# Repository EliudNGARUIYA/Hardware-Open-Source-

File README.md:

# Hardware-Open-Source-
Random hardware projects I'm working on like this one here on Home Automation...

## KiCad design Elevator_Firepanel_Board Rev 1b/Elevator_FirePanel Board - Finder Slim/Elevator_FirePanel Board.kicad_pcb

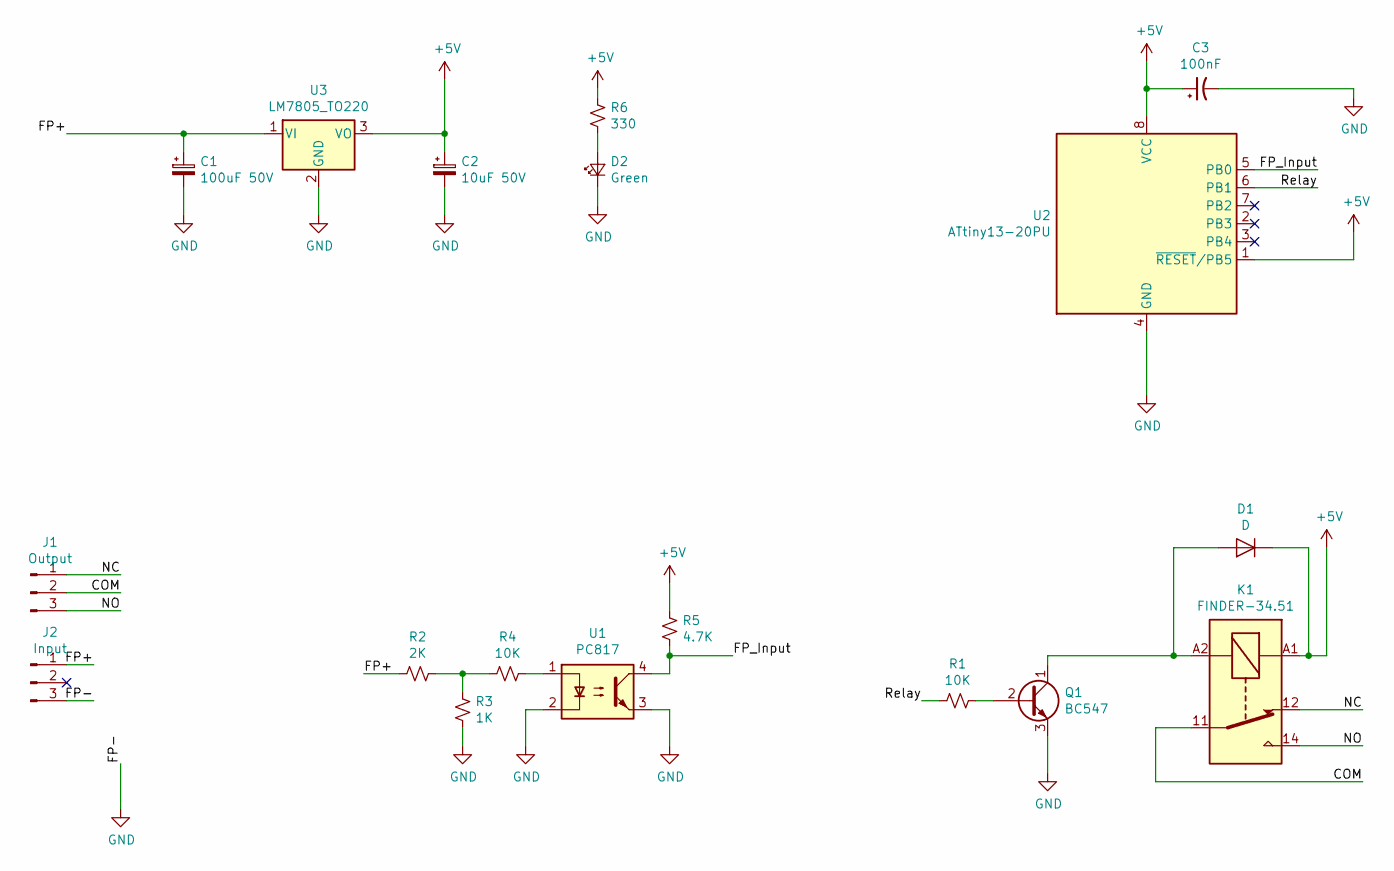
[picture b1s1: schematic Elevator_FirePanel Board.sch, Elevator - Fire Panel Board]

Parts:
C1: 100uF 50V; CP_Radial_D8.0mm_P2.50mm
C2: 10uF 50V; CP_Radial_D8.0mm_P2.50mm
C3: 100nF; CP_Radial_Tantal_D4.5mm_P2.50mm
D1: D; D_5W_P12.70mm_Horizontal
D2: Green; LED_D3.0mm
J1: Output; PhoenixContact_MSTBA_2,5_3-G_1x03_P5.00mm_Horizontal
J2: Input; Wago_734-133_1x03_P3.50mm_Vertical
K1: FINDER-34.51; Relay_SPDT_Finder_34.51_Vertical
Q1: BC547; TO-92_Inline
R1, R4: 10K; R_Axial_DIN0207_L6.3mm_D2.5mm_P10.16mm_Horizontal
R2: 2K; R_Axial_DIN0207_L6.3mm_D2.5mm_P10.16mm_Horizontal
R3: 1K; R_Axial_DIN0207_L6.3mm_D2.5mm_P10.16mm_Horizontal
R5: 4.7K; R_Axial_DIN0207_L6.3mm_D2.5mm_P10.16mm_Horizontal
R6: 330; R_Axial_DIN0207_L6.3mm_D2.5mm_P10.16mm_Horizontal
U1: PC817; DIP-4_W7.62mm
U2: ATtiny13-20PU; DIP-8_W7.62mm
U3: LM7805_TO220; TO-220-3_Vertical

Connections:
+5V: C2.1, C3.1, D1.1 (K), K1.A1, R5.2, R6.2, U2.1 (~RESET~/PB5), U2.8 (VCC), U3.3 (VO)
/COM: J1.2, K1.11
/FP+: C1.1, J2.1, R2.2, U3.1 (VI)
/FP_Input: R5.1, U1.4, U2.5 (PB0)
/NC: J1.1, K1.12
/NO: J1.3, K1.14
/Relay: R1.2, U2.6 (PB1)
GND: C1.2, C2.2, C3.2, D2.1 (K), J2.3, Q1.3 (E), R3.1, U1.2, U1.3, U2.4 (GND), U3.2 (GND)
unnamed: D1.2 (A), K1.A2, Q1.1 (C)
unnamed: D2.2 (A), R6.1
unnamed: Q1.2 (B), R1.1
unnamed: R2.1, R3.2, R4.2
unnamed: R4.1, U1.1

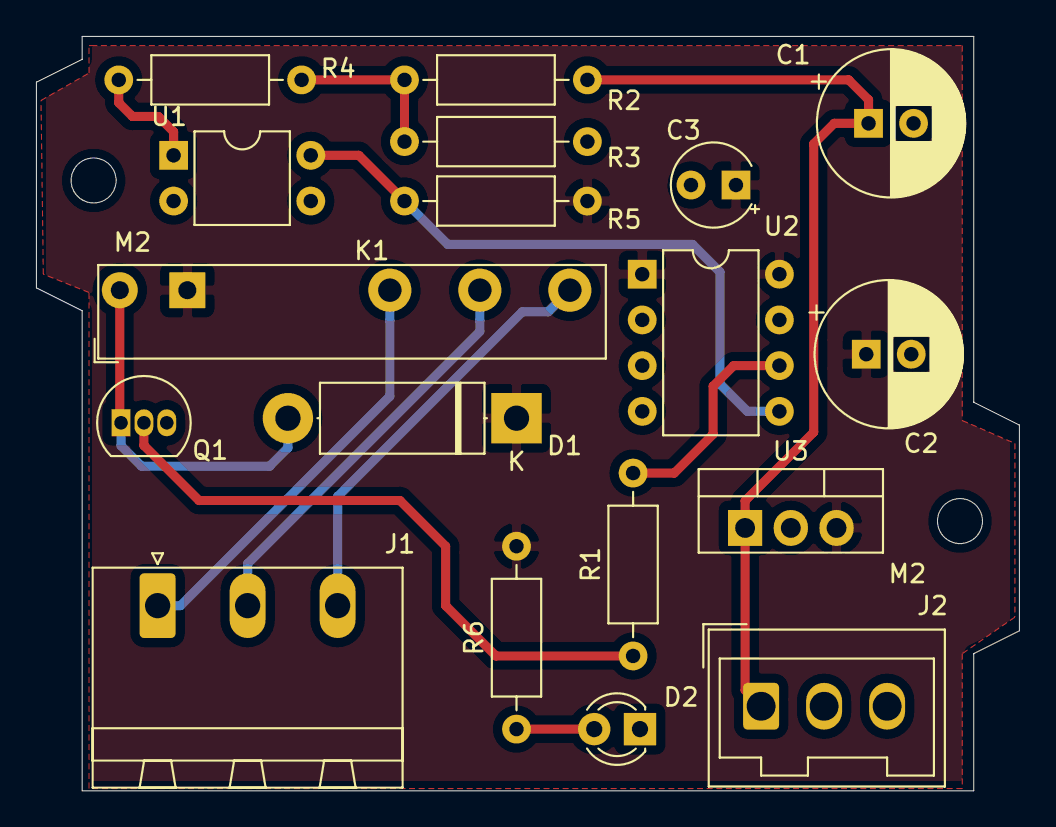
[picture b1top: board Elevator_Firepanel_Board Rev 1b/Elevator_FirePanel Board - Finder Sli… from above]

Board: 2 copper layers, 54.6 x 41.9 mm, 20 parts (0 on the bottom side), 13 nets.

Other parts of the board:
M2, M2#2: MountingHole_2.5mm

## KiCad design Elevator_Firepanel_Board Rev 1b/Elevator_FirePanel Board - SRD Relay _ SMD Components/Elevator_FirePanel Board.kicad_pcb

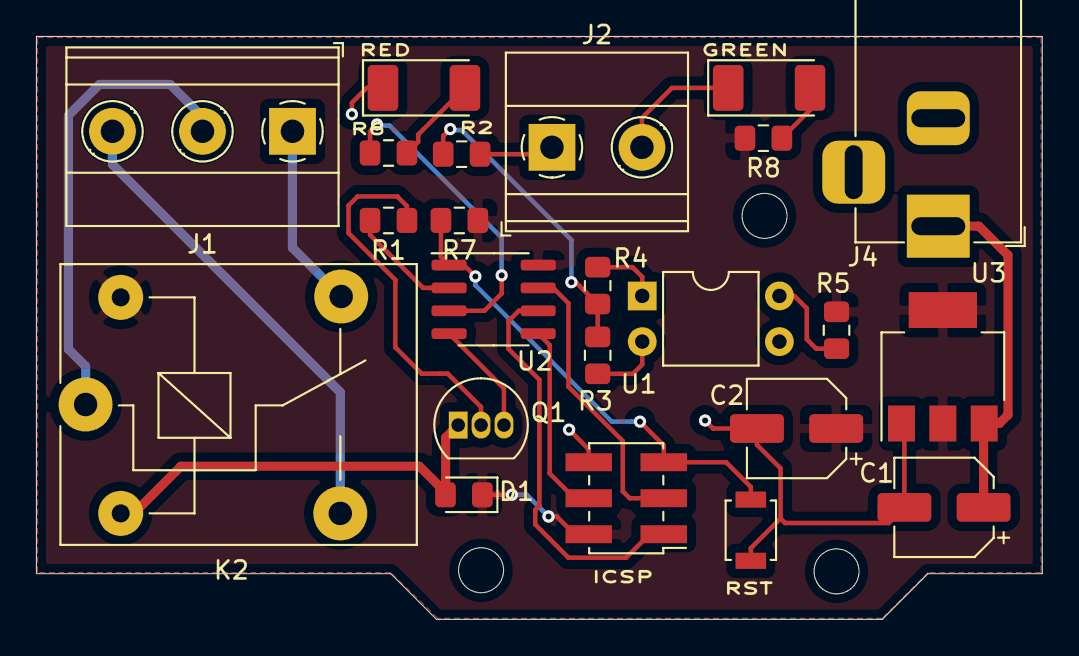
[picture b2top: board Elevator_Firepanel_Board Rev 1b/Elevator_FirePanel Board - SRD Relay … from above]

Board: 2 copper layers, 55.9 x 32.4 mm, 23 parts (0 on the bottom side), 20 nets.

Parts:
C1: 100uF 35V; CP_Elec_5x5.4
C2: 10uF 35V; CP_Elec_5x5.4
D1: D; D_0805_2012Metric_Pad1.15x1.40mm_HandSolder
GREEN: LED; LED_2010_5025Metric_Castellated
ICSP: ICSP; PinHeader_2x03_P2.00mm_Vertical_SMD
J1: Output; TerminalBlock_Phoenix_MKDS-1,5-3_1x03_P5.00mm_Horizontal
J2: Input; TerminalBlock_Phoenix_MKDS-1,5-2_1x02_P5.00mm_Horizontal
J4: DC_IN; BarrelJack_Horizontal
K2: SANYOU_SRD_Form_C; Relay_SPDT_SANYOU_SRD_Series_Form_C
Q1: BC547; TO-92_Inline
R1, R4, R7: 10K; R_0805_2012Metric_Pad1.15x1.40mm_HandSolder
R2: 2K; R_0805_2012Metric_Pad1.15x1.40mm_HandSolder
R3: 1K; R_0805_2012Metric_Pad1.15x1.40mm_HandSolder
R5: 4.7K; R_0805_2012Metric_Pad1.15x1.40mm_HandSolder
R6, R8: 330; R_0805_2012Metric_Pad1.15x1.40mm_HandSolder
RED: Green; LED_2010_5025Metric_Castellated
RST: SW_Push; SW_SPST_B3U-1000P
U1: PC817; DIP-4_W7.62mm
U2: ATtiny13-20SSU; SOIC-8_3.9x4.9mm_P1.27mm
U3: AMS1117-5.0; SOT-223-3_TabPin2

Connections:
+5V: C2.1, D1.1, ICSP.2, K2.5, R5.2, R7.1, R8.2, U2.8, U3.2
+12V: C1.1, J4.1, U3.3
/FP_Input: R5.1, U1.4
/Rela_y: R6.2, U2.3
/Relay: R1.2, U2.2
GND: C1.2, C2.2, GREEN.1, ICSP.6, J2.2, J4.2, Q1.3, R3.1, RED.1, RST.2, U1.2, U1.3, U2.4, U3.1
MISO: ICSP.1, U2.6
MOSI: ICSP.4, U2.5
unnamed: D1.2, K2.2, Q1.1
unnamed: R6.1, RED.2
unnamed: GREEN.2, R8.1
unnamed: J1.1, K2.4
unnamed: J1.2, K2.1
unnamed: J1.3, K2.3
unnamed: J2.1, R2.2
unnamed: Q1.2, R1.1
unnamed: R2.1, R3.2, R4.2
unnamed: R4.1, U1.1
PB2: ICSP.3, U2.7
Reset: ICSP.5, R7.2, RST.1, U2.1

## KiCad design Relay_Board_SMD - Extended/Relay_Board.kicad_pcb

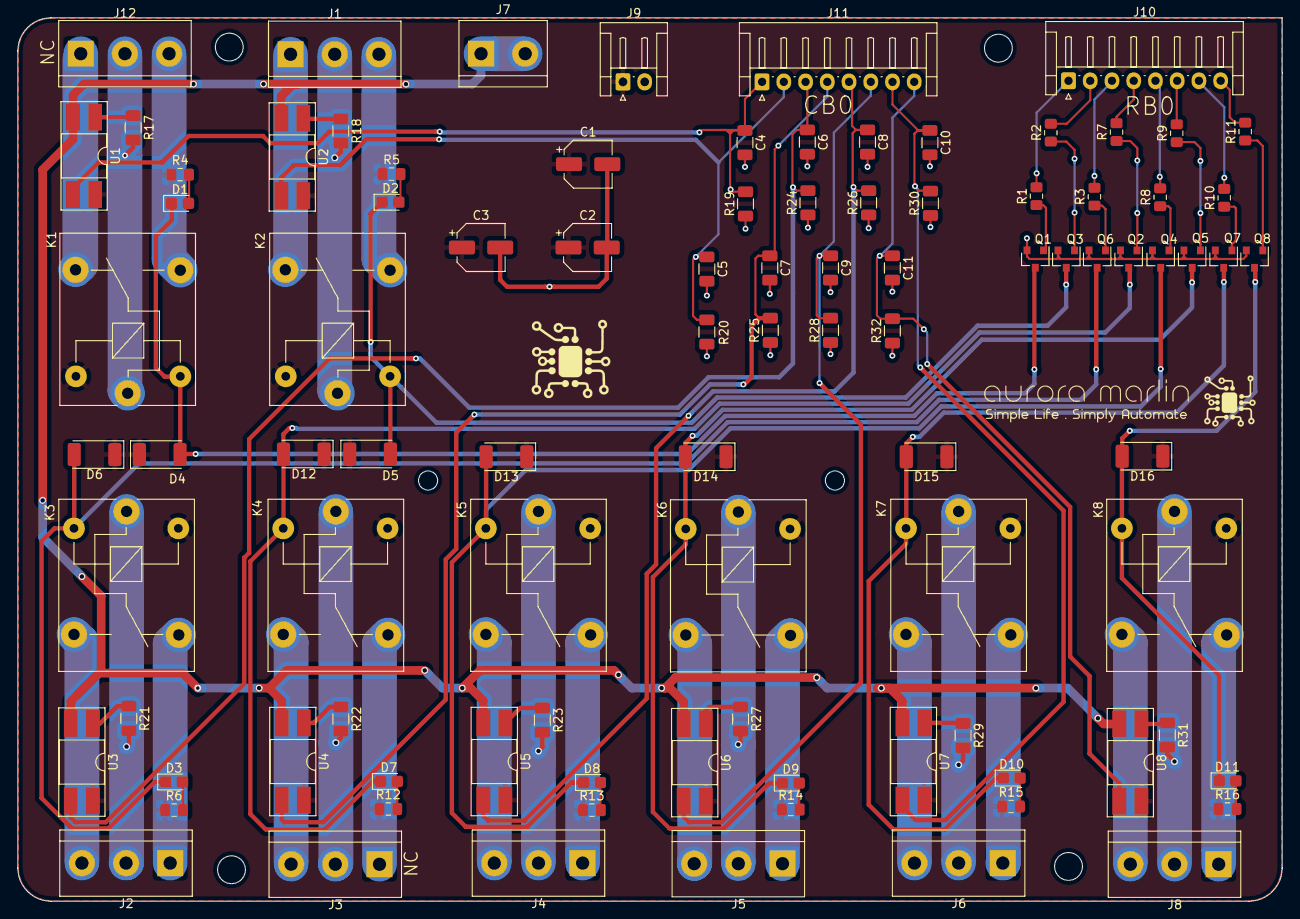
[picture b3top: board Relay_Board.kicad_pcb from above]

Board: 2 copper layers, 145.4 x 101.6 mm, 95 parts (0 on the bottom side), 75 nets.

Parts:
C1: 470uF 25V; CP_Elec_5x5.4
C2: 100uF 25V; CP_Elec_5x5.4
C3: 10uF 25v; CP_Elec_5x5.4
C4, C5, C6, C7, C8, C9, C10, C11: 10uF; C_1206_3216Metric
D1, D2, D3, D7, D8, D9, D10, D11: RED; LED_0805_2012Metric_Castellated
D4, D5, D6, D12, D13, D14, D15, D16: 1N4007; D_2010_5025Metric_Pad1.52x2.65mm_HandSolder
J1, J2, J3, J4, J5, J6, J8, J12: Relay OUT; TerminalBlock_bornier-3_P5.08mm
J7: AC_IN; TerminalBlock_bornier-2_P5.08mm
J9: 5VDC; JST_EH_S2B-EH_1x02_P2.50mm_Horizontal
J10: MCU; JST_EH_S8B-EH_1x08_P2.50mm_Horizontal
J11: OPTO; JST_EH_S8B-EH_1x08_P2.50mm_Horizontal
K1, K2, K3, K4, K5, K6, K7, K8: SANYOU_SRD_Form_C; Relay_SPDT_SANYOU_SRD_Series_Form_C
Q1, Q2, Q3, Q4, Q5, Q6, Q7, Q8: BC847; SOT-23
R1, R2, R3, R7, R8, R9, R10, R11: 10K; R_0805_2012Metric_Pad1.15x1.40mm_HandSolder
R4, R5, R6, R12, R13, R14, R15, R16: 330; R_0805_2012Metric_Pad1.15x1.40mm_HandSolder
R17, R18, R21, R22, R23, R27, R29, R31: 200K; R_1206_3216Metric
R19, R20, R24, R25, R26, R28, R30, R32: 100K; R_1206_3216Metric
U1, U2, U3, U4, U5, U6, U7, U8: EL814; DIP-4_W8.89mm_SMDSocket_LongPads

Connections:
240_N: J7.1, J7.2, U1.2, U2.2, U3.2, U4.2, U5.2, U6.2, U7.2, U8.2
+5V: C1.1, C2.1, C3.1, D4.1, D5.1, D6.1, D12.1, D13.1, D14.1, D15.1, D16.1, J9.1, K1.5, K2.5, K3.5, K4.5, K5.5, K6.5, K7.5, K8.5, R4.1, R5.1, R6.1, R12.1, R13.1, R14.1, R15.1, R16.1, U1.4, U2.4, U3.4, U4.4, U5.4, U6.4, U7.4, U8.4
/L1: J12.1, K1.4
/L2: J1.1, K2.4
/L3: J2.1, K3.4
/L4: J3.1, K4.4
/L5: J4.1, K5.4
/L6: J5.1, K6.4
/L7: J6.1, K7.4
/L8: J8.1, K8.4
/RR_1: J12.3, K1.3
/RR_2: J1.3, K2.3
/RR_3: J2.3, K3.3
/RR_4: J3.3, K4.3
/RR_5: J4.3, K5.3
/RR_6: J5.3, K6.3
/RR_7: J6.3, K7.3
/RR_8: J8.3, K8.3
/Relay_1: J10.1, R1.2
/Relay_2: J10.2, R2.2
/Relay_3: J10.3, R3.2
/Relay_4: J10.4, R7.2
/Relay_5: J10.5, R8.2
/Relay_6: J10.6, R9.2
/Relay_7: J10.7, R10.2
/Relay_8: J10.8, R11.2
COM1: J12.2, K1.1, R17.2
COM2: J1.2, K2.1, R18.2
COM3: J2.2, K3.1, R21.2
COM4: J3.2, K4.1, R22.2
COM5: J4.2, K5.1, R23.2
COM6: J5.2, K6.1, R27.2
COM7: J6.2, K7.1, R29.2
COM8: J8.2, K8.1, R31.2
GND: C1.2, C2.2, C3.2, C4.2, C5.2, C6.2, C7.2, C8.2, C9.2, C10.2, C11.2, J9.2, Q1.2, Q2.2, Q3.2, Q4.2, Q5.2, Q6.2, Q7.2, Q8.2, R19.1, R20.1, R24.1, R25.1, R26.1, R28.1, R30.1, R32.1
unnamed: D1.1, D4.2, K1.2, Q1.3
unnamed: D1.2, R4.2
unnamed: D2.1, D5.2, K2.2, Q3.3
unnamed: D2.2, R5.2
unnamed: D3.1, D6.2, K3.2, Q6.3
unnamed: D3.2, R6.2
unnamed: D7.2, R12.2
unnamed: D8.2, R13.2
unnamed: D9.2, R14.2
unnamed: D10.1, D15.2, K7.2, Q7.3
unnamed: D10.2, R15.2
unnamed: D11.1, D16.2, K8.2, Q8.3
unnamed: D11.2, R16.2
unnamed: D7.1, D12.2, K4.2, Q2.3
unnamed: D8.1, D13.2, K5.2, Q4.3
unnamed: D9.1, D14.2, K6.2, Q5.3
unnamed: Q1.1, R1.1
unnamed: Q2.1, R7.1
unnamed: Q3.1, R2.1
unnamed: Q4.1, R8.1
unnamed: Q5.1, R9.1
unnamed: Q6.1, R3.1
unnamed: Q7.1, R10.1
unnamed: Q8.1, R11.1
unnamed: R17.1, U1.1
unnamed: R18.1, U2.1
unnamed: R21.1, U3.1
unnamed: R22.1, U4.1
unnamed: R23.1, U5.1
unnamed: R27.1, U6.1
unnamed: R29.1, U7.1
unnamed: R31.1, U8.1
OUT1: C4.1, J11.1, R19.2, U1.3
OUT2: C5.1, J11.2, R20.2, U2.3
OUT3: C6.1, J11.3, R24.2, U3.3
OUT4: C7.1, J11.4, R25.2, U4.3
OUT5: C8.1, J11.5, R26.2, U5.3
OUT6: C9.1, J11.6, R28.2, U6.3
OUT7: C10.1, J11.7, R30.2, U7.3
OUT8: C11.1, J11.8, R32.2, U8.3

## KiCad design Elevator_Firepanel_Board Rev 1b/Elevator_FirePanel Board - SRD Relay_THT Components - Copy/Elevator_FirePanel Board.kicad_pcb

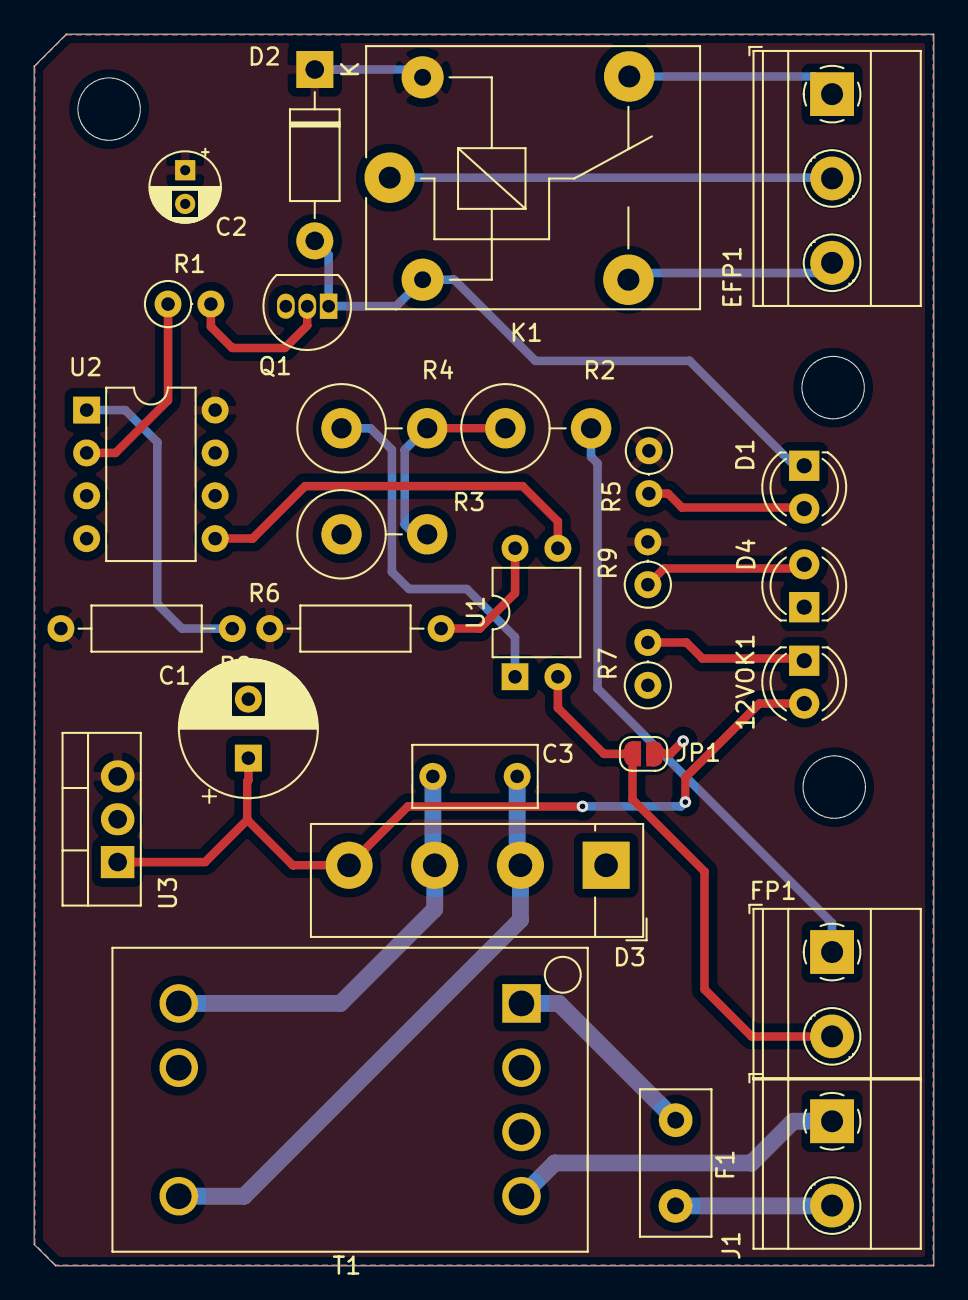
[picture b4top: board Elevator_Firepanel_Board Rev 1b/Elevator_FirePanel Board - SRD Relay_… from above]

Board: 2 copper layers, 53.3 x 73.0 mm, 28 parts (0 on the bottom side), 24 nets.

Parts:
12VOK1: Blue; LED_D4.0mm
C1: 100uF 35V; CP_Radial_D8.0mm_P3.50mm
C2: 10uF 35V; CP_Radial_D4.0mm_P2.00mm
C3: 1uF 400V; C_Rect_L7.2mm_W3.5mm_P5.00mm_FKS2_FKP2_MKS2_MKP2
D1: Red; LED_D4.0mm
D2: 1N4001; D_DO-41_SOD81_P10.16mm_Horizontal
D3: D_Bridge_-AA+; Diode_Bridge_Vishay_KBL
D4: Green; LED_D4.0mm
EFP1: Output; TerminalBlock_Phoenix_MKDS-1,5-3_1x03_P5.00mm_Horizontal
F1: 2A; Fuse_Littelfuse_395Series
FP1: Input; TerminalBlock_Phoenix_MKDS-1,5-2_1x02_P5.00mm_Horizontal
J1: AC_IN; TerminalBlock_Phoenix_MKDS-1,5-2_1x02_P5.00mm_Horizontal
JP1: GROUND; SolderJumper-2_P1.3mm_Open_RoundedPad1.0x1.5mm
K1: SANYOU_SRD_Form_C; Relay_SPDT_SANYOU_SRD_Series_Form_C
Q1: BC547; TO-92_Inline
R1: 10K; R_Axial_DIN0207_L6.3mm_D2.5mm_P2.54mm_Vertical
R2: 2K 1/2W; R_Axial_DIN0516_L15.5mm_D5.0mm_P5.08mm_Vertical
R3: 1K 1/2W; R_Axial_DIN0516_L15.5mm_D5.0mm_P5.08mm_Vertical
R4: 10K 1/2W; R_Axial_DIN0516_L15.5mm_D5.0mm_P5.08mm_Vertical
R5, R7, R9: 330; R_Axial_DIN0207_L6.3mm_D2.5mm_P2.54mm_Vertical
R6: 4.7K; R_Axial_DIN0207_L6.3mm_D2.5mm_P10.16mm_Horizontal
R8: 10K; R_Axial_DIN0207_L6.3mm_D2.5mm_P10.16mm_Horizontal
T1: Transformer_1P_1S_SO8; Transformer_Microphone_Lundahl_LL1587
U1: PC817; DIP-4_W7.62mm
U2: ATtiny13-20PU; DIP-8_W7.62mm
U3: LM7805_TO220; TO-220-3_Vertical

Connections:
+5V: C2.1, D2.1, K1.5, R5.1, R6.2, R8.1, R9.2, U2.8, U3.3
+12V: 12VOK1.2, C1.1, D3.4, U3.1
/ACL: F1.2, J1.2
/ACL_2: C3.1, D3.2, T1.8
/ACN: J1.1, T1.4
/ACN_2: C3.2, D3.3, T1.5
/Relay: R1.1, U2.2
GND: C1.2, C2.2, D3.1, D4.1, JP1.2, Q1.3, R3.1, R7.1, U2.4, U3.2
MOSI: U1.3, U2.5
unnamed: 12VOK1.1, R7.2
unnamed: D1.1, D2.2, K1.2, Q1.1
unnamed: D1.2, R5.2
unnamed: D4.2, R9.1
unnamed: EFP1.1, K1.4
unnamed: EFP1.2, K1.1
unnamed: EFP1.3, K1.3
unnamed: F1.1, T1.1
unnamed: FP1.1, R2.2
unnamed: FP1.2, JP1.1, U1.2
unnamed: Q1.2, R1.2
unnamed: R2.1, R3.2, R4.2
unnamed: R4.1, U1.1
unnamed: R6.1, U1.4
Reset: R8.2, U2.1

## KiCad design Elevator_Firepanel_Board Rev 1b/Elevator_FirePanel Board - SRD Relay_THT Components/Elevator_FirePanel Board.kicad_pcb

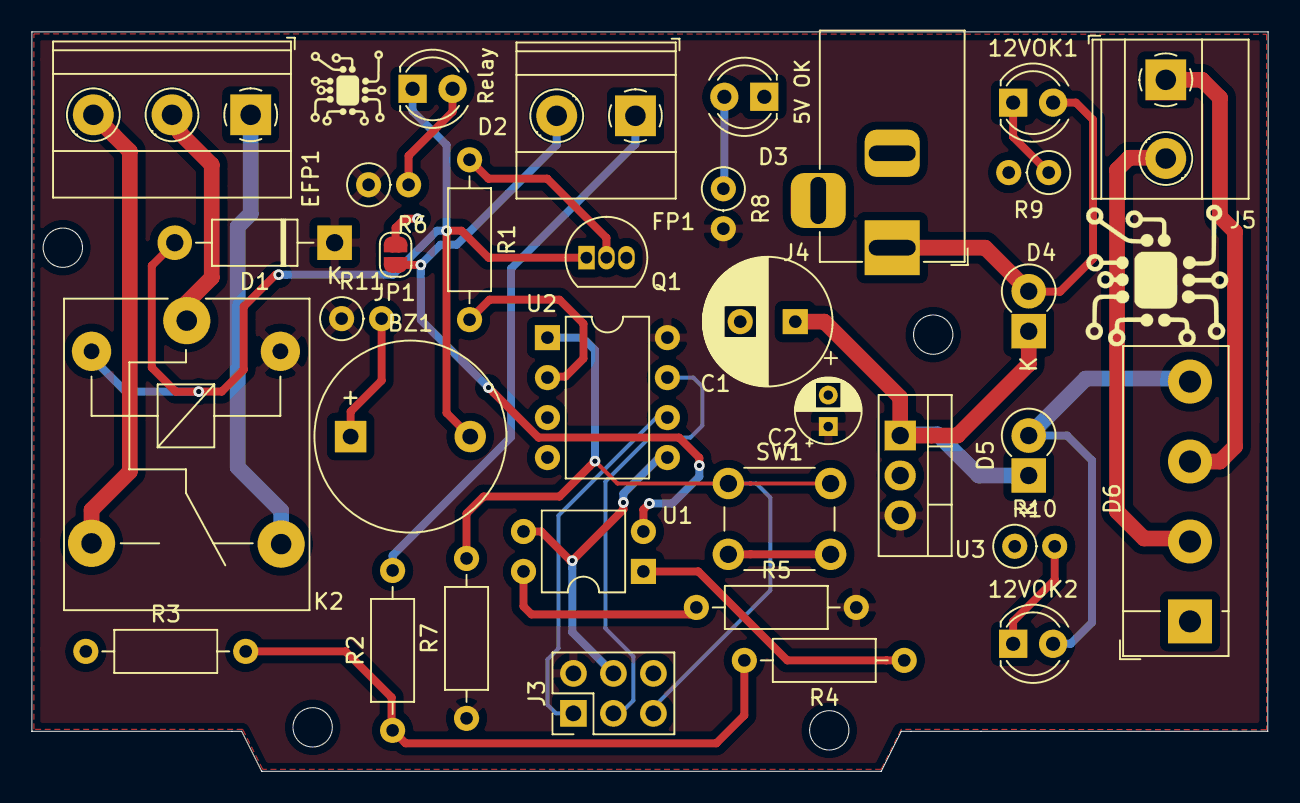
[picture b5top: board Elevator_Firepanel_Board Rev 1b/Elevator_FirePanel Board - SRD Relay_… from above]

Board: 2 copper layers, 78.6 x 47.0 mm, 34 parts (0 on the bottom side), 27 nets.

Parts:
12VOK1: Yellow; LED_D4.0mm
12VOK2: Blue; LED_D4.0mm
BZ1: Buzzer; Buzzer_12x9.5RM7.6
C1: 100uF 35V; CP_Radial_D8.0mm_P3.50mm
C2: 10uF 35V; CP_Radial_D4.0mm_P2.00mm
D1: 1N4001; D_DO-41_SOD81_P10.16mm_Horizontal
D2: Red; LED_D4.0mm
D3: Green; LED_D4.0mm
D4, D5: D; D_DO-41_SOD81_P2.54mm_Vertical_KathodeUp
D6: D_Bridge_-AA+; Diode_Bridge_Vishay_KBL
EFP1: Output; TerminalBlock_Phoenix_MKDS-1,5-3_1x03_P5.00mm_Horizontal
FP1: Input; TerminalBlock_Phoenix_MKDS-1,5-2_1x02_P5.00mm_Horizontal
J3: ICSP; PinHeader_2x03_P2.54mm_Vertical
J4: DC_IN; BarrelJack_Horizontal
J5: AC_IN; TerminalBlock_Phoenix_MKDS-1,5-2_1x02_P5.00mm_Horizontal
JP1: GROUND; SolderJumper-2_P1.3mm_Open_RoundedPad1.0x1.5mm
K2: SANYOU_SRD_Form_C; Relay_SPDT_SANYOU_SRD_Series_Form_C
Q1: BC547; TO-92_Inline
R1, R7: 10K; R_Axial_DIN0207_L6.3mm_D2.5mm_P10.16mm_Horizontal
R2: 2K 1/2W; R_Axial_DIN0207_L6.3mm_D2.5mm_P10.16mm_Horizontal
R3: 1K 1/2W; R_Axial_DIN0207_L6.3mm_D2.5mm_P10.16mm_Horizontal
R4: 10K 1/2W; R_Axial_DIN0207_L6.3mm_D2.5mm_P10.16mm_Horizontal
R5: 4.7K; R_Axial_DIN0207_L6.3mm_D2.5mm_P10.16mm_Horizontal
R6, R8, R9, R10: 330; R_Axial_DIN0207_L6.3mm_D2.5mm_P2.54mm_Vertical
R11: 180; R_Axial_DIN0207_L6.3mm_D2.5mm_P2.54mm_Vertical
SW1: SW_Push; SW_PUSH_6mm_H4.3mm
U1: PC817; DIP-4_W7.62mm
U2: ATtiny13-20PU; DIP-8_W7.62mm
U3: LM7805_TO220; TO-220-3_Vertical

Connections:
+5V: C2.1, D1.1, J3.2, K2.5, R5.2, R6.1, R7.1, R8.2, R11.1, U2.8, U3.3
+12V: C1.1, D4.1, D5.1, U3.1
/ACL: D6.2, J5.2
/ACN: D6.3, J5.1
/DC+: 12VOK2.2, D5.2, D6.4
/Relay: R1.2, U2.2
GND: C1.2, C2.2, D3.1, D6.1, J3.6, J4.2, JP1.2, Q1.3, R3.1, R9.2, R10.1, SW1.2, U2.4, U3.2
MISO: J3.1, U2.6
MOSI: J3.4, U1.3, U2.5
unnamed: 12VOK1.1, R9.1
unnamed: 12VOK1.2, D4.2, J4.1
unnamed: 12VOK2.1, R10.2
unnamed: BZ1.1, R11.2
unnamed: BZ1.2, D1.2, D2.1, K2.2, Q1.1
unnamed: D2.2, R6.2
unnamed: D3.2, R8.1
unnamed: EFP1.1, K2.4
unnamed: EFP1.2, K2.1
unnamed: EFP1.3, K2.3
unnamed: FP1.1, R2.2
unnamed: FP1.2, JP1.1, U1.2
unnamed: Q1.2, R1.1
unnamed: R2.1, R3.2, R4.2
unnamed: R4.1, U1.1
unnamed: R5.1, U1.4
PB2: J3.3, U2.7
Reset: J3.5, R7.2, SW1.1, U2.1

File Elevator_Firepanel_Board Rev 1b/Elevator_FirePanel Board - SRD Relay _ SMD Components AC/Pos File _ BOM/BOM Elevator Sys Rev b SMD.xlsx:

version | source | date | tool | number | name | tstamps | title | company | rev | date2 | source3 | number4 | value | ref | value5 | footprint | datasheet | lib | part | description | names | tstamps6 | tstamp | lib7 | part8 | description9 | docs | fp | field | name10 | num | name11 | type | alias | logical | uri | code | name12 | ref13 | pin
 |  |  |  |  |  |  |  |  |  |  |  |  | Checked By : Reuben G
 |  |  |  |  |  |  |  |  |  |  |  |  | Designed By : Eliud NGARUIYA
 |  |  |  |  |  |  |  |  |  |  |  |  |  | J1 | Output | TerminalBlock_Phoenix:TerminalBlock_Phoenix_MKDS-1,5-3_1x03_P5.00mm_Horizontal | ~ | Connector | Conn_01x03_Male | Generic connector, single row, 01x03, script generated (kicad-library-utils/sch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 | / | / | 5CF42365
 |  |  |  |  |  |  |  |  |  |  |  |  |  | D1 | D | Diode_SMD:D_0805_2012Metric_Pad1.15x1.40mm_HandSolder | ~ | Device | D | Diode | / | / | 5CF472F1
 |  |  |  |  |  |  |  |  |  |  |  |  |  | R1 | 10K | Resistor_SMD:R_0805_2012Metric_Pad1.15x1.40mm_HandSolder | ~ | Device | R_Small_US | Resistor, small US symbol | / | / | 5CF49B4E
 |  |  |  |  |  |  |  |  |  |  |  |  |  | D2 | Green | LED_SMD:LED_2010_5025Metric_Castellated | ~ | Device | LED_Small | Light emitting diode, small symbol | / | / | 5CF9ECF9
 |  |  |  |  |  |  |  |  |  |  |  |  |  | R6 | 330 | Resistor_SMD:R_0805_2012Metric_Pad1.15x1.40mm_HandSolder | ~ | Device | R_Small_US | Resistor, small US symbol | / | / | 5CFA0037
 |  |  |  |  |  |  |  |  |  |  |  |  |  | J2 | Input | TerminalBlock_Phoenix:TerminalBlock_Phoenix_MKDS-1,5-2_1x02_P5.00mm_Horizontal | ~ | Connector | Conn_01x02_Male | Generic connector, single row, 01x02, script generated (kicad-library-utils/sch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 | / | / | 5CF48D9A
 |  |  |  |  |  |  |  |  |  |  |  |  |  | Q1 | BC547 | Package_TO_SOT_THT:TO-92_Inline | http://www.fairchildsemi.com/ds/BC/BC547.pdf | Transistor_BJT | BC547 | 0.1A Ic, 45V Vce, Small Signal NPN Transistor, TO-92 | / | / | 5CF5E51A
 |  |  |  |  |  |  |  |  |  |  |  |  |  | R8 | 330 | Resistor_SMD:R_0805_2012Metric_Pad1.15x1.40mm_HandSolder | ~ | Device | R_US | Resistor, US symbol | / | / | 5D015A01
 |  |  |  |  |  |  |  |  |  |  |  |  |  | SW1 | SW_Push | Button_Switch_SMD:SW_SPST_B3U-1000P |  | Switch | SW_Push | Push button switch, generic, two pins | / | / | 5D015A16
 |  |  |  |  |  |  |  |  |  |  |  |  |  | D3 | LED | LED_SMD:LED_2010_5025Metric_Castellated | ~ | Device | LED | Light emitting diode | / | / | 5D015A1D
 |  |  |  |  |  |  |  |  |  |  |  |  |  | J4 | AC_IN | TerminalBlock:TerminalBlock_Altech_AK300-2_P5.00mm | ~ | Connector | Conn_01x02_Male | Generic connector, single row, 01x02, script generated (kicad-library-utils/sch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 | / | / | 5D015A24
 |  |  |  |  |  |  |  |  |  |  |  |  |  | C1 | 100uF 35V | Capacitor_SMD:CP_Elec_5x5.4 | ~ | Device | CP_Small | Polarized capacitor, small symbol | / | / | 5D015A3D
 |  |  |  |  |  |  |  |  |  |  |  |  |  | C2 | 10uF 35V | Capacitor_SMD:CP_Elec_5x5.4 | ~ | Device | CP_Small | Polarized capacitor, small symbol | / | / | 5D015A44
 |  |  |  |  |  |  |  |  |  |  |  |  |  | R7 | 10K | Resistor_SMD:R_0805_2012Metric_Pad1.15x1.40mm_HandSolder | ~ | Device | R_US | Resistor, US symbol | / | / | 5D015AE2
 |  |  |  |  |  |  |  |  |  |  |  |  |  | J3 | ICSP | Connector_PinHeader_2.00mm:PinHeader_2x03_P2.00mm_Vertical_SMD | ~ | Connector_Generic | Conn_02x03_Odd_Even | Generic connector, double row, 02x03, odd/even pin numbering scheme (row 1 odd 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 | / | / | 5D015B0A
 |  |  |  |  |  |  |  |  |  |  |  |  |  | K2 | SANYOU_SRD_Form_C | Relay_THT:Relay_SPDT_SANYOU_SRD_Series_Form_C | http://www.sanyourelay.ca/public/products/pdf/SRD.pdf | Relay | SANYOU_SRD_Form_C | Sanyo SRD relay, Single Pole Miniature Power Relay, | / | / | 5CF5533A
 |  |  |  |  |  |  |  |  |  |  |  |  |  | R5 | 4.7K | Resistor_SMD:R_0805_2012Metric_Pad1.15x1.40mm_HandSolder | ~ | Device | R_Small_US | Resistor, small US symbol | / | / | 5CF52362
 |  |  |  |  |  |  |  |  |  |  |  |  |  | R3 | 1K | Resistor_SMD:R_0805_2012Metric_Pad1.15x1.40mm_HandSolder | ~ | Device | R_Small_US | Resistor, small US symbol | / | / | 5CF51EBE
 |  |  |  |  |  |  |  |  |  |  |  |  |  | R2 | 2K | Resistor_SMD:R_0805_2012Metric_Pad1.15x1.40mm_HandSolder | ~ | Device | R_Small_US | Resistor, small US symbol | / | / | 5CF51BC8
 |  |  |  |  |  |  |  |  |  |  |  |  |  | R4 | 10K | Resistor_SMD:R_0805_2012Metric_Pad1.15x1.40mm_HandSolder | ~ | Device | R_Small_US | Resistor, small US symbol | / | / | 5CF515CC
 |  |  |  |  |  |  |  |  |  |  |  |  |  | U1 | PC817 | Package_DIP:DIP-4_W7.62mm | http://www.soselectronic.cz/a_info/resource/d/pc817.pdf | Isolator | PC817 | DC Optocoupler, Vce 35V, CTR 50-300%, DIP4 | / | / | 5CF5027C
 |  |  |  |  |  |  |  |  |  |  |  |  |  | U2 | ATtiny13-20SSU | Package_SO:SOIC-8_3.9x4.9mm_P1.27mm | http://ww1.microchip.com/downloads/en/DeviceDoc/doc2535.pdf | MCU_Microchip_ATtiny | ATtiny13-20SSU | 20MHz, 1kB Flash, 64B SRAM, 64B EEPROM, debugWIRE, SOIC-8 | / | / | 5D21BC6E
 |  |  |  |  |  |  |  |  |  |  |  |  |  | U3 | AMS1117-5.0 | Package_TO_SOT_SMD:SOT-223-3_TabPin2 | http://www.advanced-monolithic.com/pdf/ds1117.pdf | Regulator_Linear | AMS1117-5.0 | 1A Low Dropout regulator, positive, 5.0V fixed output, SOT-223 | / | / | 5D21DAEE
 |  |  |  |  |  |  |  |  |  |  |  |  |  | D4 | D_Bridge_-AA+ | Diode_THT:Diode_Bridge_19.0x3.5x10.0mm_P5.0mm | ~ | Device | D_Bridge_-AA+ | Diode bridge, -ve/AC/AC/+ve | / | / | 5D1E322A

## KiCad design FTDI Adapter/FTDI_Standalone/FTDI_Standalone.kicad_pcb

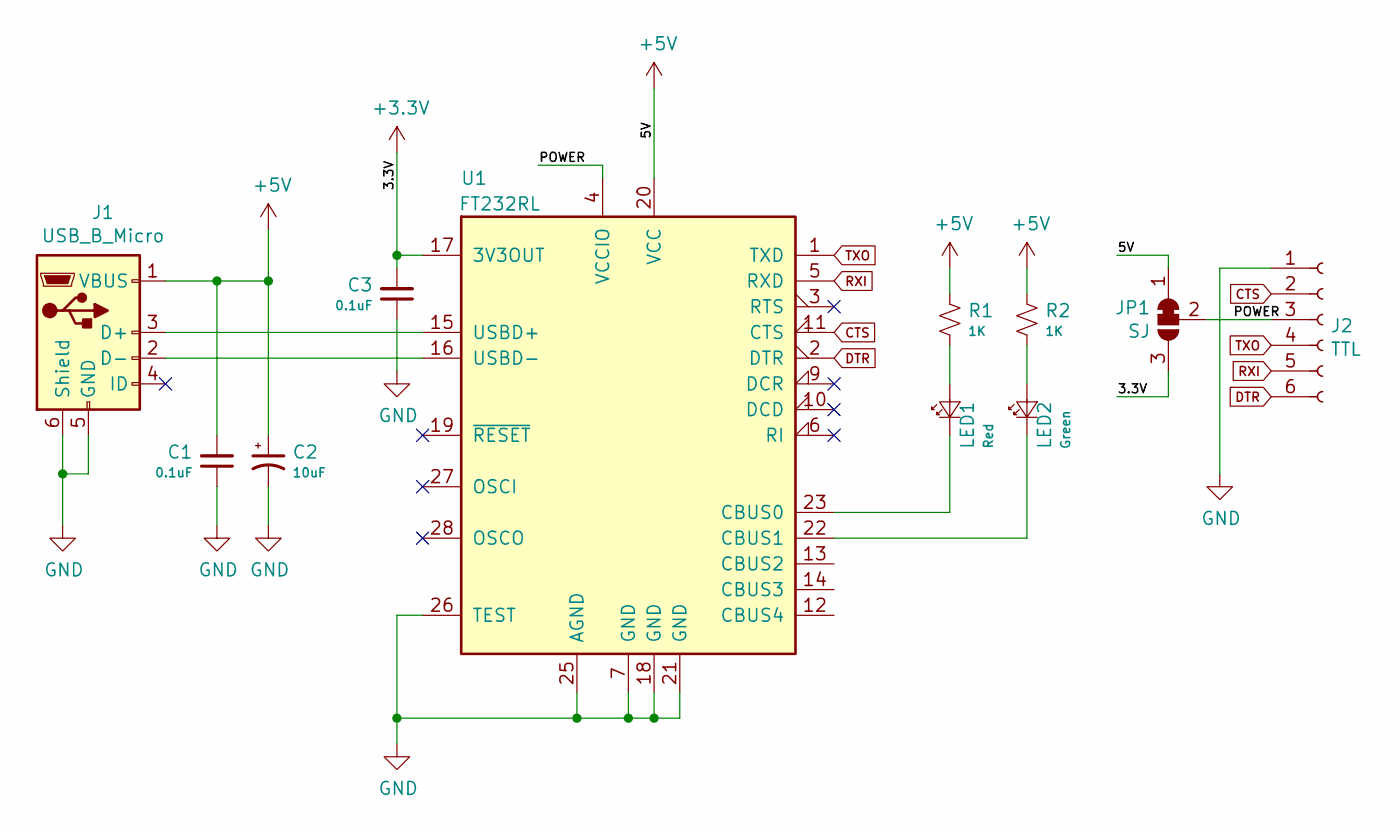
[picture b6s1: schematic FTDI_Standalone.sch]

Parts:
C1, C3: 0.1uF; C_0805_2012Metric_Pad1.15x1.40mm_HandSolder
C2: 10uF; CP_Elec_4x4.5
J1: USB_B_Micro; USB_Micro-B_GCT_USB3076-30-A
J2: TTL; PinHeader_1x06_P2.00mm_Horizontal
JP1: SJ; SolderJumper-3_P1.3mm_Open_RoundedPad1.0x1.5mm
LED1: Red; LED_0805_2012Metric_Pad1.15x1.40mm_HandSolder
LED2: Green; LED_0805_2012Metric_Pad1.15x1.40mm_HandSolder
R1, R2: 1K; R_0805_2012Metric_Pad1.15x1.40mm_HandSolder
U1: FT232RL; SSOP-28_5.3x10.2mm_P0.65mm

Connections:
+3V3: C3.2, JP1.3 (B), U1.17 (3V3OUT)
+5V: C1.2, C2.1, J1.1 (VBUS), JP1.1 (A), R1.1, R2.1, U1.20 (VCC)
/POWER: J2.3, JP1.2 (C), U1.4 (VCCIO)
CTS: J2.2, U1.11 (CTS)
DTR: J2.6, U1.2 (DTR)
GND: C1.1, C2.2, C3.1, J1.5 (GND), J1.6 (Shield), J2.1, U1.7 (GND), U1.18 (GND), U1.21 (GND), U1.25 (AGND), U1.26 (TEST)
unnamed: J1.2 (D-), U1.16 (USBD-)
unnamed: J1.3 (D+), U1.15 (USBD+)
unnamed: LED1.1 (K), U1.23 (CBUS0)
unnamed: LED1.2 (A), R1.2
unnamed: LED2.1 (K), U1.22 (CBUS1)
unnamed: LED2.2 (A), R2.2
RXI: J2.5, U1.5 (RXD)
TXO: J2.4, U1.1 (TXD)

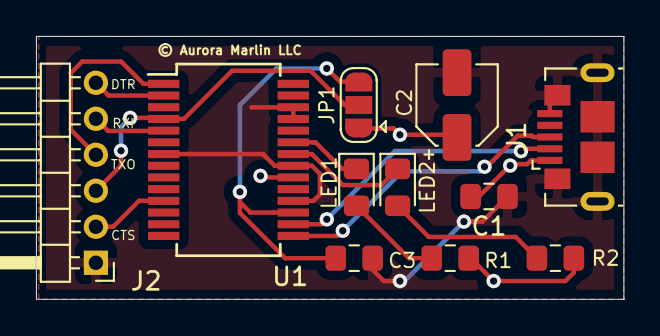
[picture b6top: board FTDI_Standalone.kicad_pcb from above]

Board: 2 copper layers, 32.6 x 14.6 mm, 11 parts (0 on the bottom side), 14 nets.

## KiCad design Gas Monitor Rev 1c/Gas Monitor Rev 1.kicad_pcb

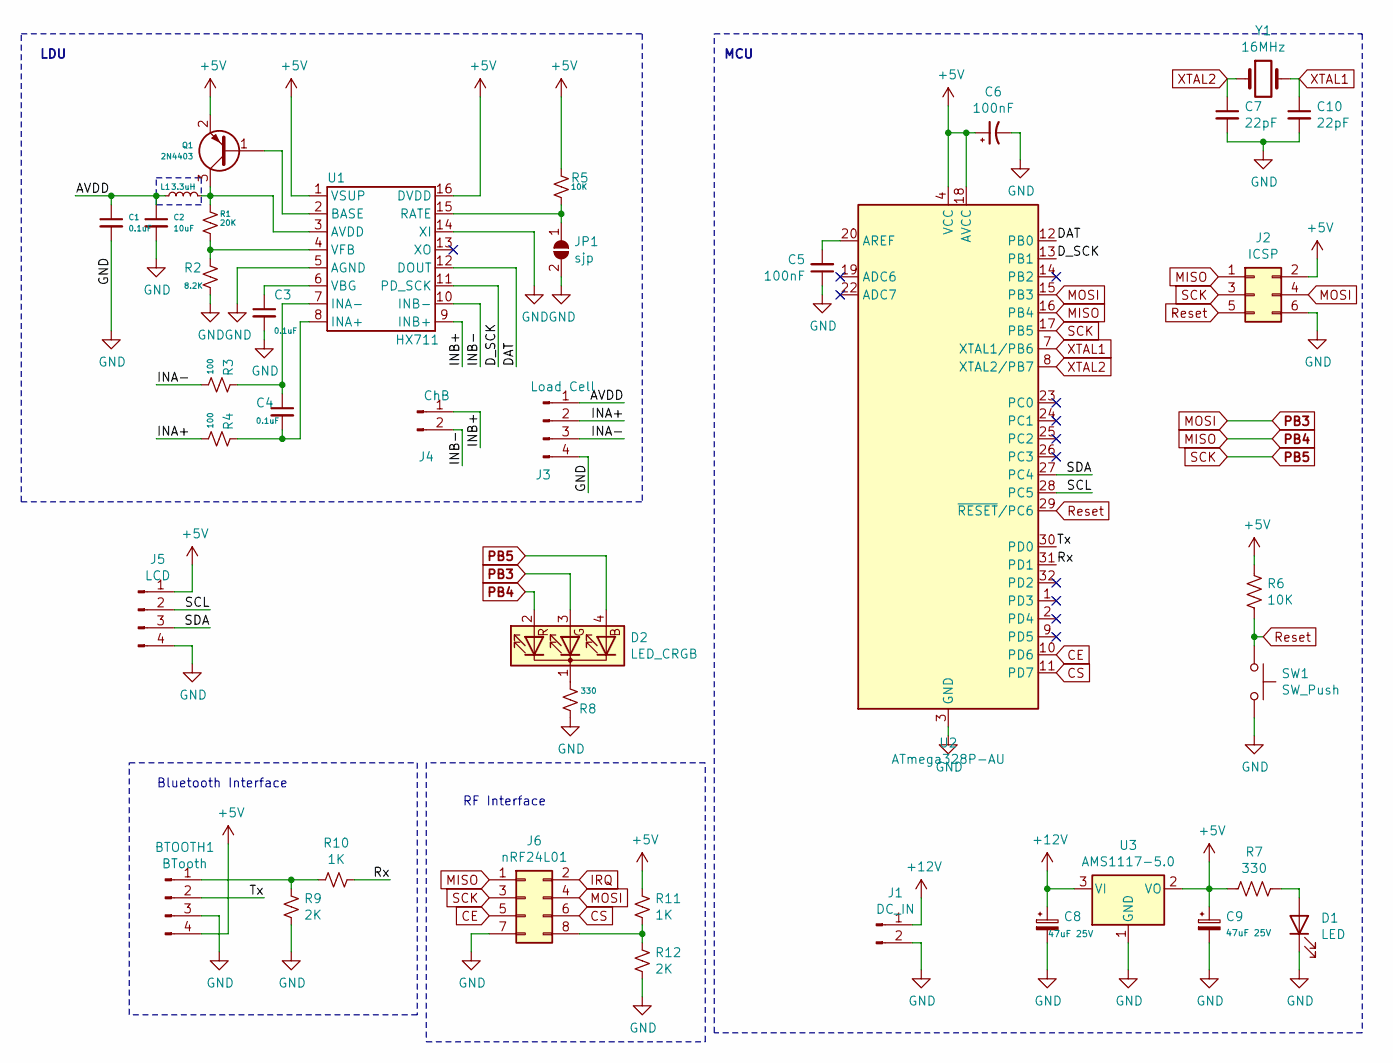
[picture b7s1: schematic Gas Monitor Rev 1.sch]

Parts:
BTOOTH1: BTooth; PinHeader_1x04_P2.54mm_Vertical
C1, C3, C4: 0.1uF; C_0805_2012Metric_Pad1.15x1.40mm_HandSolder
C2: 10uF; C_0805_2012Metric_Pad1.15x1.40mm_HandSolder
C5: 100nF; C_0805_2012Metric_Pad1.15x1.40mm_HandSolder
C6: 100nF; CP_EIA-1608-08_AVX-J_Pad1.25x1.05mm_HandSolder
C7, C10: 22pF; C_0805_2012Metric_Pad1.15x1.40mm_HandSolder
C8, C9: 47uF 25V; CP_Elec_5x5.4
D1: LED; LED_2010_5025Metric_Castellated
D2: LED_CRGB; LED_D5.0mm-4_RGB
J1: DC_IN; BarrelJack_Horizontal
J2: ICSP; PinHeader_2x03_P2.54mm_Vertical_SMD
J3: Load Cell; JST_EH_S4B-EH_1x04_P2.50mm_Horizontal
J4: ChB; JST_EH_S2B-EH_1x02_P2.50mm_Horizontal
J5: LCD; JST_EH_S4B-EH_1x04_P2.50mm_Horizontal
J6: nRF24L01; PinHeader_2x04_P2.54mm_Vertical
JP1: sjp; SolderJumper-2_P1.3mm_Open_RoundedPad1.0x1.5mm
L1: 3.3uH; L_6.3x6.3_H3
Q1: 2N4403; SOT-23
R1: 20K; R_2010_5025Metric_Pad1.52x2.65mm_HandSolder
R2: 8.2K; R_2010_5025Metric_Pad1.52x2.65mm_HandSolder
R3: 100; R_0805_2012Metric_Pad1.15x1.40mm_HandSolder
R4: 100; R_1210_3225Metric
R5, R6: 10K; R_2010_5025Metric_Pad1.52x2.65mm_HandSolder
R7, R8: 330; R_0805_2012Metric_Pad1.15x1.40mm_HandSolder
R9, R12: 2K; R_0805_2012Metric_Pad1.15x1.40mm_HandSolder
R10, R11: 1K; R_0805_2012Metric_Pad1.15x1.40mm_HandSolder
SW1: SW_Push; SW_SPST_B3U-1000P
U1: HX711; SOP-16_4.4x10.4mm_P1.27mm
U2: ATmega328P-AU; TQFP-32_7x7mm_P0.8mm
U3: AMS1117-5.0; SOT-223-3_TabPin2
Y1: 16MHz; Crystal_HC49-4H_Vertical

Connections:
+5V: BTOOTH1.4, C6.1, C9.1, J2.2, J5.1, Q1.2 (E), R5.1, R6.1, R7.2, R11.2, U1.1 (VSUP), U1.16 (DVDD), U2.4 (VCC), U2.6 (VCC), U2.18 (AVCC), U3.2 (VO)
+12V: C8.1, J1.1, U3.3 (VI)
/AVDD: C1.1, C2.1, J3.1, L1.1
/DAT: U1.12 (DOUT), U2.12 (PB0)
/D_SCK: U1.11 (PD_SCK), U2.13 (PB1)
/INA+: J3.2, R4.2
/INA-: J3.3, R3.2
/INB+: J4.1, U1.9 (INB+)
/INB-: J4.2, U1.10 (INB-)
/Rx: R10.1, U2.31 (PD1)
/SCL: J5.2, U2.28 (PC5)
/SDA: J5.3, U2.27 (PC4)
/Tx: BTOOTH1.2, U2.30 (PD0)
CE: J6.5, U2.10 (PD6)
CS: J6.6, U2.11 (PD7)
GND: BTOOTH1.3, C1.2, C2.2, C3.2, C5.1, C6.2, C7.2, C8.2, C9.2, C10.2, D1.1 (K), J1.2, J2.6, J3.4, J5.4, J6.7, JP1.2 (B), R2.2, R8.1, R9.2, R12.2, SW1.2, U1.5 (AGND), U1.14 (XI), U2.3 (GND), U2.5 (GND), U2.21 (GND), U3.1 (GND)
MISO: D2.2 (RA), J2.1, J6.1, U2.16 (PB4)
MOSI: D2.3 (GA), J2.4, J6.4, U2.15 (PB3)
unnamed: BTOOTH1.1, R9.1, R10.2
unnamed: C3.1, U1.6 (VBG)
unnamed: C4.1, R3.1, U1.7 (INA-)
unnamed: C4.2, R4.1, U1.8 (INA+)
unnamed: C5.2, U2.20 (AREF)
unnamed: D1.2 (A), R7.1
unnamed: D2.1 (K), R8.2
unnamed: J6.8, R11.1, R12.1
unnamed: JP1.1 (A), R5.2, U1.15 (RATE)
unnamed: L1.2, Q1.3 (C), R1.1, U1.3 (AVDD)
unnamed: Q1.1 (B), U1.2 (BASE)
unnamed: R1.2, R2.1, U1.4 (VFB)
PB5: D2.4 (BA), J2.3, J6.3, U2.17 (PB5)
Reset: J2.5, R6.2, SW1.1, U2.29 (~RESET~/PC6)
XTAL1: C10.1, U2.7 (XTAL1/PB6), Y1.2
XTAL2: C7.1, U2.8 (XTAL2/PB7), Y1.1

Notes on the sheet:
MCU
LDU
RF Interface
Bluetooth Interface

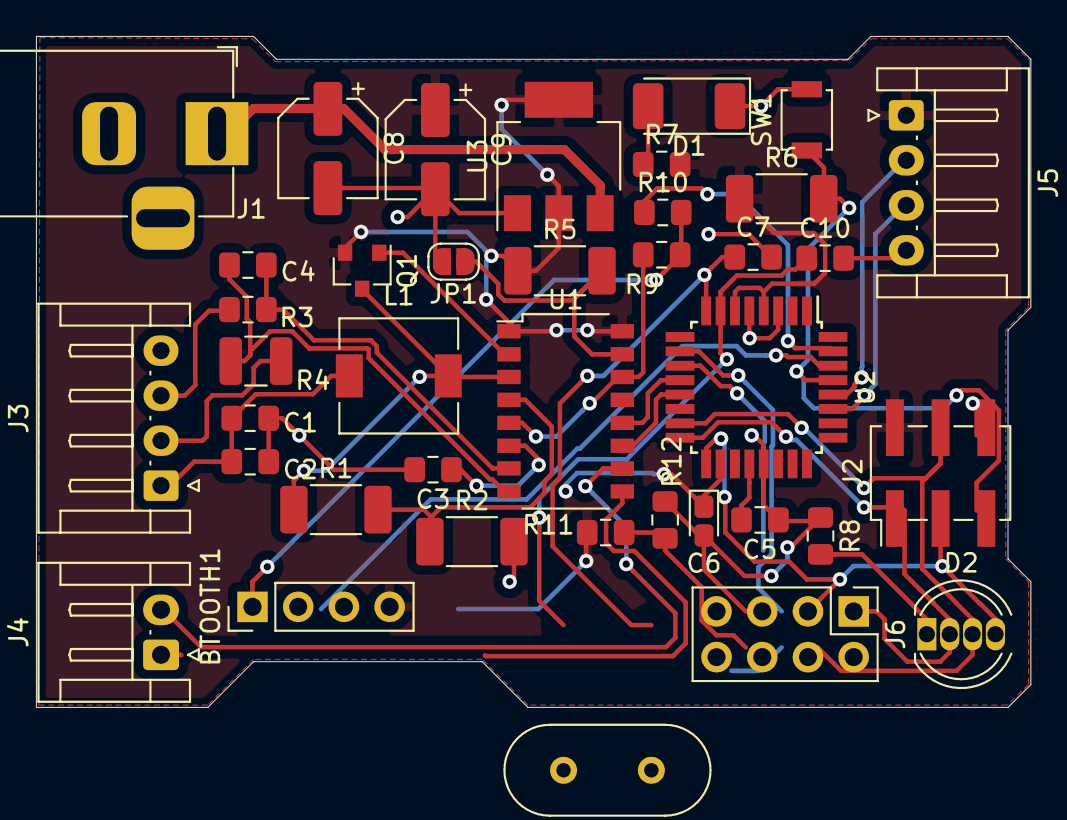
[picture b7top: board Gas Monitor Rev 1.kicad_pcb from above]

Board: 2 copper layers, 55.2 x 37.3 mm, 39 parts (0 on the bottom side), 34 nets.

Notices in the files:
Elevator_Firepanel_Board Rev 1b/Elevator_FirePanel Board - SRD Relay_THT Components/Elevator_FirePanel Board-Aurora-Marlin.kicad_pcb:
© Aurora Marlin LLC
FTDI Adapter/FTDI_Standalone/FTDI_Standalone.kicad_pcb:
© Aurora Marlin LLC - 2019
Relay_Board_SMD - Extended/Relay_Board.kicad_pcb:
© Aurora Marlin, Inc
